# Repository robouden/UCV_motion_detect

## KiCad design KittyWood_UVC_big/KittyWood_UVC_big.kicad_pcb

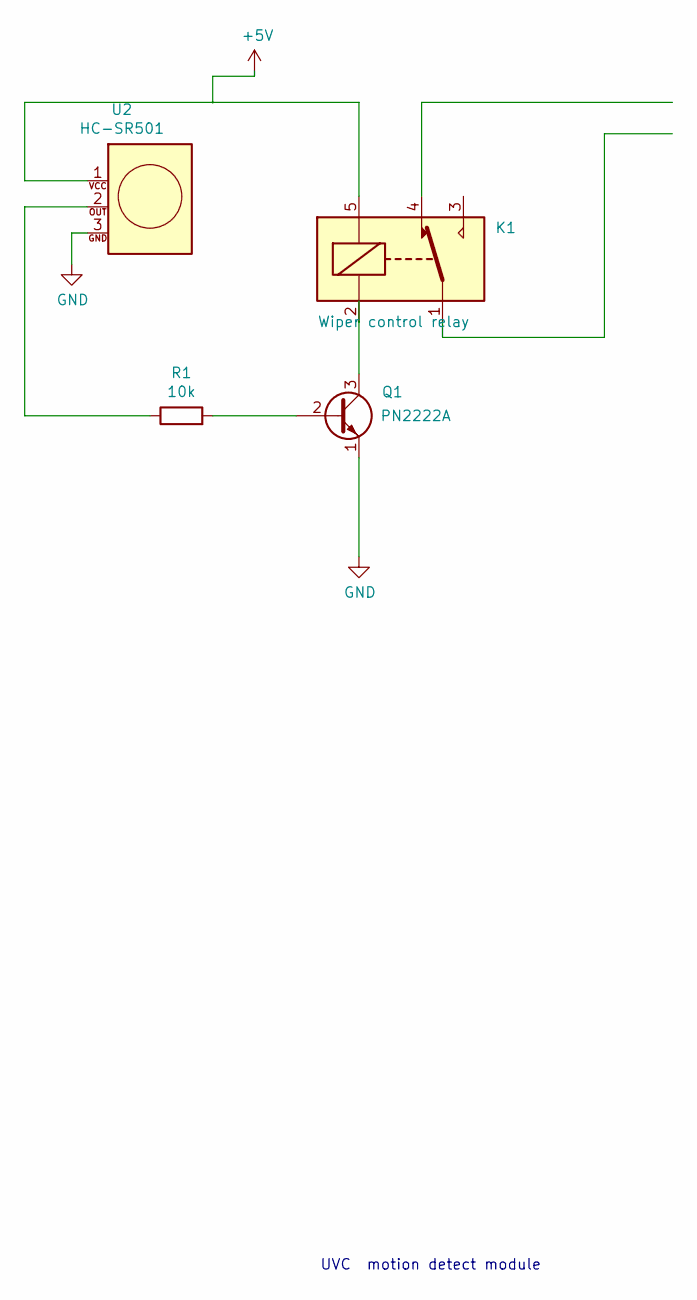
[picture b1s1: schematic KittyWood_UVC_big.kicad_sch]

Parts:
K1: Wiper control relay; Relay_SPDT_SANYOU_SRD_Series_Form_C
Q1: PN2222A; TO-92_Inline
R1: 10k; R_Axial_DIN0207_L6.3mm_D2.5mm_P7.62mm_Horizontal
U2: HC-SR501

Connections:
+5V: K1.5, U2.1
GND: Q1.1 (E), U2.3
unnamed: K1.2, Q1.3 (C)
unnamed: Q1.2 (B), R1.2
unnamed: R1.1, U2.2

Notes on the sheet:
UVC motion detect module

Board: 2 copper layers, 4 parts (0 on the bottom side), 5 nets, no tracks yet.

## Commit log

2020-10-15 start
2020-10-15 Updated PCB
2021-03-02 test
